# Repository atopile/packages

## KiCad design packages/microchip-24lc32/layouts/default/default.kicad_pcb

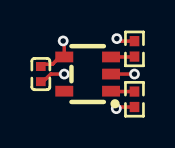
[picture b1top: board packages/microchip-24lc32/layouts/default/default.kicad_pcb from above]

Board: 2 copper layers, 4 parts (0 on the bottom side), 4 nets.

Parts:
C1: 1F; C0402
R1, R2: 10000Ω; R0402
U1: SOT-23-5_L2.9-W1.6-P0.95-LS2.7-BR

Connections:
SCL: R1.1, U1.1
SDA: R2.1, U1.3
hv: C1.1, R1.2, R2.2, U1.4
lv: C1.2, U1.2

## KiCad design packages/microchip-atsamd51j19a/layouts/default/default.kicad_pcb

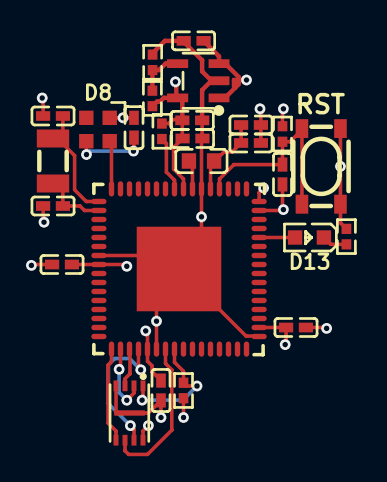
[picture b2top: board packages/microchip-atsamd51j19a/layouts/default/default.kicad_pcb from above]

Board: 2 copper layers, 26 parts (0 on the bottom side), 20 nets.

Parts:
C1, C2: 22pF ±5% 50V C0G; C0402
C3, C4, C5, C6, C11: 100nF ±10% 16V X7R; C0402
C7, C8, C12, C14: 1µF ±10% 25V X5R; C0402
C13: 10µF ±20% 6.3V X5R; C0402
L1: 10µH ±20% 20MHz 50mA 1.17Ω; L0603
LED1: LED-SMD_4P-L2.0-W2.0-BR
LED2: LED0603-RD
R1, R3, R4, R5: 10kΩ ±1% 62.5mW; R0402
R2: 20kΩ ±1% 62.5mW; R0402
R6: 100Ω ±1% 62.5mW; R0402
SW1: KEY-SMD_4P-L4.2-W3.2-P2.20-LS4.6
U1: SOT-23-5_L3.0-W1.7-P0.95-LS2.8-BL
U2: QFN-64_L9.0-W9.0-P0.50-TL-EP4.7
U3: USON-8_L3.0-W2.0-P0.50-BL-EP
X1: FC-135R_L3.2-W1.5

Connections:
3V3: C3.1, C4.1, C5.1, C6.1, C8.1, C11.1, LED1.1, R2.1, R3.1, R4.2, R5.2, U1.5, U2.8, U2.21, U2.34, U2.48, U2.56, U3.8
5V: C7.1, U1.1, U1.3
-gnd-0: C1.2, C2.2, C3.2, C4.2, C5.2, C6.2, C7.2, C8.2, C11.2, C14.2, LED1.3, R1.2, R6.1, SW1.1, SW1.2, U1.2, U2.7, U2.22, U2.33, U2.47, U2.54, U2.65, U3.4, U3.9
-gnd-1: C12.2, C13.2
-line-2: U2.17, U3.5
-line-3: U2.18, U3.2
-line-4: U2.19, U3.3
-line-5: U2.20, U3.7
-line-6: R5.1, U2.57
ADJ_NC: R1.1, R2.2, U1.4
CLK: U2.23, U3.6
D13: LED2.2, U2.44
K: LED2.1, R6.2
NEOPIXEL: LED1.4, U2.64
RESETN: C14.1, R3.2, SW1.3, SW1.4, U2.52
VDDCORE: C12.1, C13.1, L1.2, U2.53
VSW: L1.1, U2.55
nCS: R4.1, U2.24, U3.1
xin: C1.1, U2.1, X1.1
xout: C2.1, U2.2, X1.2

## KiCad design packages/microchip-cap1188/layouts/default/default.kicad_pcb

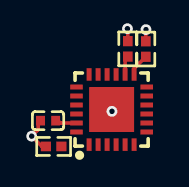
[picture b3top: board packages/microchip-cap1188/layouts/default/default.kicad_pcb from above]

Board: 2 copper layers, 5 parts (0 on the bottom side), 5 nets.

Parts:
C1: 1F; C0402
R1: 100000Ω; R0402
R2, R3: 10000Ω; R0402
U1: QFN-24_L4.0-W4.0-P0.50-BL-EP2.5

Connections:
ADDR_COMM: R1.1, U1.14
RESET: R3.1, U1.24
hv: C1.1, R2.2, U1.23
lv: C1.2, R1.2, R3.2, U1.25
nALERT_nBC_IRQ: R2.1, U1.13

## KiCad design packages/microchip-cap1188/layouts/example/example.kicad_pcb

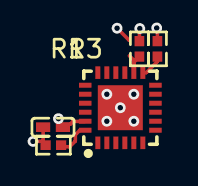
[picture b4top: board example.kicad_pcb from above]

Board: 2 copper layers, 5 parts (0 on the bottom side), 5 nets.

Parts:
C1: 100nF ±10% 16V X7R; C0402
R1: 100kΩ ±1% 62.5mW; R0402
R2, R3: 10kΩ ±1% 62.5mW; R0402
U1: QFN-24_L4.0-W4.0-P0.50-BL-EP2.5

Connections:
ADDR_COMM: R1.1, U1.14
RESET: R2.1, U1.24
gnd: C1.2, R1.2, R2.2, U1.25
hv: C1.1, R3.2, U1.23
nALERT_nBC_IRQ: R3.1, U1.13

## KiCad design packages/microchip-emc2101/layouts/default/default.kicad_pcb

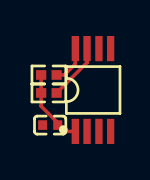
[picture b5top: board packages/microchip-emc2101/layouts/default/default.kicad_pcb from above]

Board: 2 copper layers, 4 parts (0 on the bottom side), 4 nets.

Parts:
C1: [capacitance: unknown]; C0402
R1, R2: [resistance: unknown]; R0402
U1: MSOP-8_L3.0-W3.0-P0.65-LS4.9-BL

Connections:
SCL: R1.1, U1.8
SDA: R2.1, U1.7
hv: C1.1, R1.2, R2.2, U1.1
lv: C1.2, U1.5
